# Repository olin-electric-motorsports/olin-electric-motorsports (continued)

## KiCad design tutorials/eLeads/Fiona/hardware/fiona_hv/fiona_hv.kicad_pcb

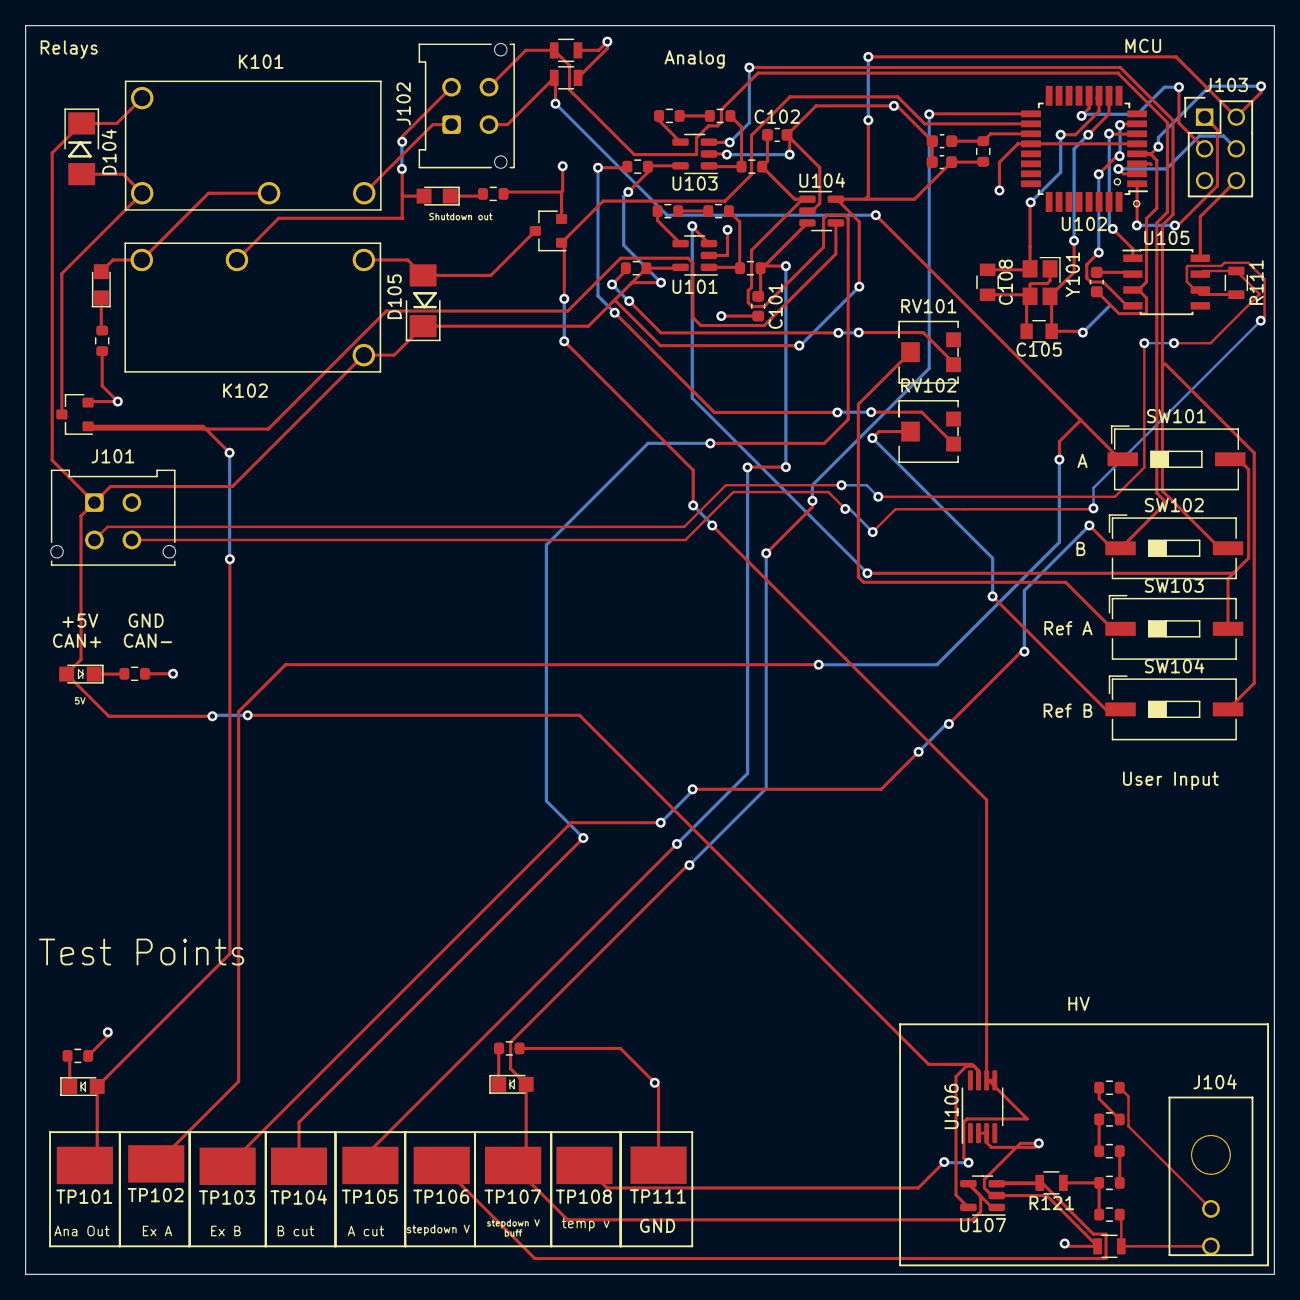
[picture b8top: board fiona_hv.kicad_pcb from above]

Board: 2 copper layers, 100.0 x 100.0 mm, 69 parts (0 on the bottom side), 48 nets.

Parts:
C101, C102: C_4.7uF; C_0603_1608Metric
C103, C107: C_0.1uF; C_0603
C104: C_100pF; C_0603
C105, C108: C_30pF; C_0805_OEM
D101, D102, D103: LED_0805; LED_0805_OEM
D104, D105: SMBJ5355B-TP; DO-214AA
D106, D107: LED_BLUE; CHIPLED_0805
J101, J102: MicroFit_VT_4
J103: CONN_02X03; Pin_Header_Straight_2x03
J104: MicroFit_RA_V_2
K101, K102: G5Q-1A4-DC5; Relay_SPST_OMRON-G5Q-1A4_OEM
Q101, Q102: SSM3K333R; SOT-23F
R101, R102, R103, R104, R105, R106, R107, R108, R109, R117, R118, R123, R124: R_1K; R_0603
R110: R_100; R_0603
R111: R_120_DNP; R_0805_OEM
R112, R113, R115, R116: R_270K; R_0603
R114: R_10K; R_0603
R119, R120, R121, R122: R_1M; R_0805_OEM
RV101, RV102: R_Potentiometer; Potentiometer_Trimmer_Bourns_TCC3
SW101, SW102, SW103, SW104: SW_DIP_x01; SW_DIP_SPSTx01_Slide_9.78x4.72mm_W8.61mm_P2.54mm
TP101, TP102, TP103, TP104, TP105, TP106, TP107, TP108, TP111: TP_SMD; Test_Point_SMD
U101, U103, U107: OpAmp; SOT-23-5
U102: ATMEGA16M1; TQFP-32_7x7mm_Pitch0.8mm
U104: LM397; SOT-23-5
U105: MCP2561-E_SN; SOIC-8_3.9x4.9mm_Pitch1.27mm_OEM
U106: AD8494; MSOP-8_3x3mm_P0.65mm
Y101: Crystal_16MHz_18pF; Crystal_SMD_FA238

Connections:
+5V: C103.1, C107.1, D101.2 (A), D104.1 (K), D105.1 (K), J101.1, J103.2, K101.5, K102.5, R101.1, R104.1, R110.1, U101.5 (V+), U102.4 (VCC), U103.5 (V+), U104.5 (V+), U105.3 (VDD), U106.7 (+Vs), U107.5 (V+)
/A: J102.3, R119.1, SW101.1, TP102.1
/B: J102.4, R120.1, SW102.1, TP103.1
/CAN+: J101.3, R111.1, U105.7 (CANH)
/CAN-: J101.4, R111.2, U105.6 (CANL)
/HV+: J104.1, R112.2
/HV-: J104.2, R114.2, R122.2
/HV_stepdown: D102.2 (A), TP107.1, U102.17 ((PCINT12/ADC8/ACMPN3/AMP1-)PC4), U107.1, U107.4 (-)
/MISO: J103.1, U102.1 ((PCINT18/PSCIN2/OC1A/MISO_A)PD2)
/MOSI: J103.4, U102.2 ((PCINT19/TXD/TXLIN/OC0A/~SS/MOSI_A)PD3)
/RXCAN: U102.7 ((PCINT11/T1/ICP1B/RXCAN)PC3), U105.4 (RXD)
/SCK: J103.3, U102.12 ((PCINT20/ADC1/RXD/RXLIN/ICP1A/SCK_A)PD4)
/SHUTDOWN_IN: J102.1, K101.3
/SHUTDOWN_OUT: D107.2 (A), J102.2, K102.2
/TXCAN: U102.6 ((PCINT10/T0/TXCAN)PC2), U105.1 (TXD)
/analog_out: D103.2 (A), Q101.1 (G), TP101.1, U104.4
/shutdown_1: D106.2 (A), K101.2, K102.3
/v_temp: Q102.1 (G), TP108.1, U102.18 ((PCINT13/ADC9/ACMP3/AMP1+)PC5), U106.5 (SENSE), U106.6
GND: C101.2, C102.2, C103.2, C104.2, C105.2, C107.2, C108.2, J101.2, J103.6, Q101.2 (S), Q102.2 (S), R109.2, R117.2, R118.2, R119.2, R120.2, R122.1, R123.2, R124.2, RV101.3, RV102.3, TP111.1, U101.2 (V-), U102.5 (GND), U102.20 (AGND), U103.2 (V-), U104.2 (V-), U105.2 (VSS), U105.8 (STBY), U106.2 (REF), U106.3 (-Vs), U107.2 (V-), Y101.2, Y101.4
unnamed: D101.1 (K), R109.1
unnamed: D102.1 (K), R117.1
unnamed: D103.1 (K), R118.1
unnamed: D104.2 (A), K101.1, Q101.3 (D)
unnamed: D105.2 (A), K102.1, Q102.3 (D)
unnamed: D106.1 (K), R123.1
unnamed: D107.1 (K), R124.1
unnamed: R101.2, RV101.1
unnamed: R102.1, R103.1
unnamed: R103.2, R107.2, U101.1
unnamed: R104.2, RV102.1
unnamed: R105.1, R106.1
unnamed: R106.2, R108.2, U103.1
unnamed: R112.1, R113.2
unnamed: R113.1, R115.2
unnamed: R114.1, R116.1, R121.1
unnamed: R115.1, R116.2
unnamed: RV101.2, SW103.1
unnamed: RV102.2, SW104.1
unnamed: SW101.2, SW103.2, U101.3 (+)
unnamed: R102.2, U101.4 (-)
unnamed: C105.1, U102.10 ((PCINT25/OC0B/XTAL1)PE1), Y101.3
unnamed: C108.1, U102.11 ((PCINT26/ADC0/XTAL2)PE2), Y101.1
unnamed: C104.1, R110.2, U102.19 (AVCC)
unnamed: SW102.2, SW104.2, U103.3 (+)
unnamed: R105.2, U103.4 (-)
unnamed: C101.1, R107.1, TP105.1, U104.3 (+)
unnamed: C102.1, R108.1, TP104.1, U104.1 (-)
unnamed: R121.2, TP106.1, U107.3 (+)
